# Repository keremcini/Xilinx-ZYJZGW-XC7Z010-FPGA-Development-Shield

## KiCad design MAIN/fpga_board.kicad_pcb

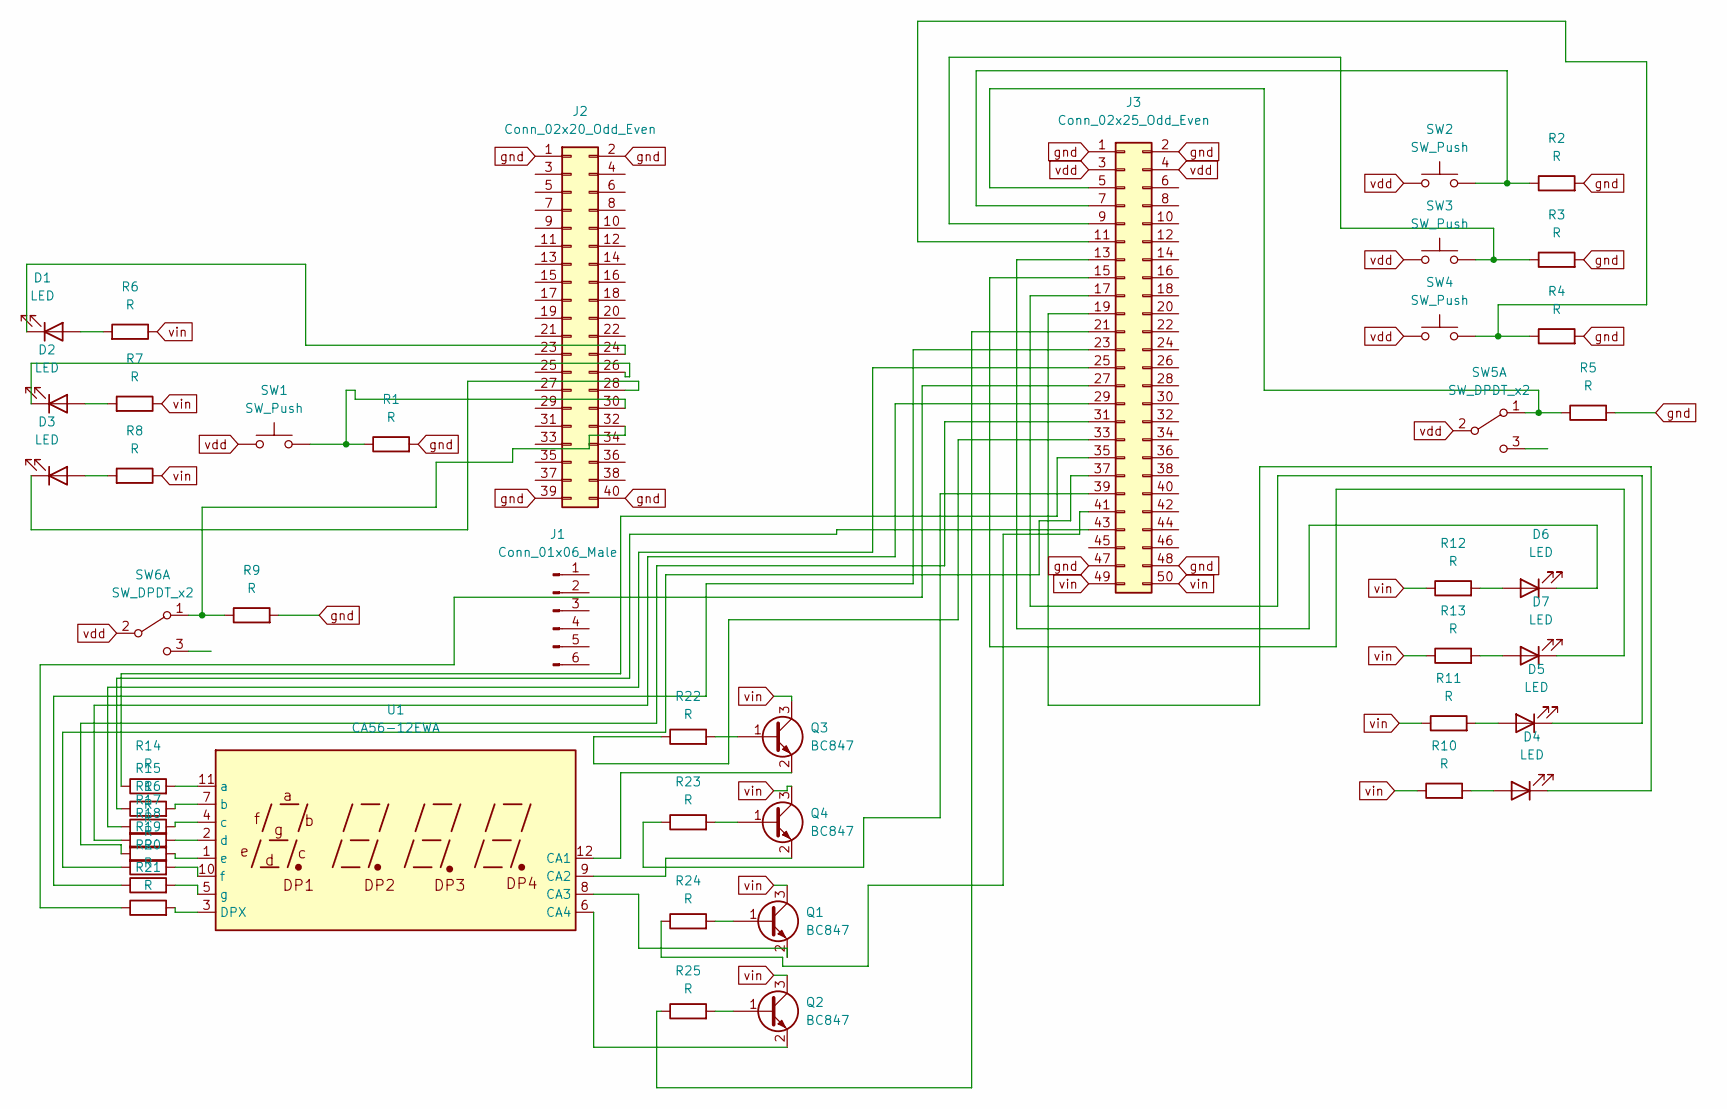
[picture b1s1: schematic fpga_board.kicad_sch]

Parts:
D1, D2, D3, D4, D5, D6, D7: LED; LED_0805_2012Metric_Pad1.15x1.40mm_HandSolder
J1: Conn_01x06_Male; PinHeader_1x06_P2.54mm_Vertical
J2: Conn_02x20_Odd_Even; PinHeader_2x20_P2.54mm_Vertical
J3: Conn_02x25_Odd_Even; PinHeader_2x25_P2.54mm_Vertical
Q1, Q2, Q3, Q4: BC847; SOT-23
R1, R2, R3, R4, R5, R6, R7, R8, R9, R10, R11, R12, R13, R14, R15, R16, R17, R18, R19, R20, R21, R22, R23, R24, R25: R; R_0805_2012Metric_Pad1.20x1.40mm_HandSolder
SW1, SW2, SW3, SW4: SW_Push; red_button
SW5, SW6: SW_DPDT_x2; switch_smd
U1: CA56-12EWA; 4_digit7_segment

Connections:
unnamed: D1.2 (A), R6.2
unnamed: D1.1 (K), J2.24
unnamed: D2.2 (A), R7.2
unnamed: D2.1 (K), J2.26
unnamed: D3.2 (A), R8.2
unnamed: D3.1 (K), J2.28
unnamed: D4.2 (A), R10.2
unnamed: D4.1 (K), J3.19
unnamed: D5.2 (A), R11.2
unnamed: D5.1 (K), J3.17
unnamed: D6.2 (A), R12.2
unnamed: D6.1 (K), J3.13
unnamed: D7.2 (A), R13.2
unnamed: D7.1 (K), J3.15
unnamed: J2.30, R1.1, SW1.2
unnamed: J2.32, R9.1, SW6.1 (A)
unnamed: J3.5, R5.1, SW5.1 (A)
unnamed: J3.7, R2.1, SW2.2
unnamed: J3.9, R3.1, SW3.2
unnamed: J3.11, R4.1, SW4.2
unnamed: J3.21, R25.1
unnamed: J3.23, R20.1
unnamed: J3.25, R16.1
unnamed: J3.27, R21.1
unnamed: J3.29, R17.1
unnamed: J3.31, R18.1
unnamed: J3.33, R22.1
unnamed: J3.35, R14.1
unnamed: J3.37, R19.1
unnamed: J3.39, R23.1
unnamed: J3.41, R24.1
unnamed: J3.43, R15.1
unnamed: Q1.1 (B), R24.2
unnamed: Q1.2 (E), U1.8 (CA3)
unnamed: Q2.1 (B), R25.2
unnamed: Q2.2 (E), U1.6 (CA4)
unnamed: Q3.1 (B), R22.2
unnamed: Q3.2 (E), U1.12 (CA1)
unnamed: Q4.1 (B), R23.2
unnamed: Q4.2 (E), U1.9 (CA2)
unnamed: R21.2, U1.3 (DPX)
unnamed: R14.2, U1.11 (a)
unnamed: R15.2, U1.7 (b)
unnamed: R16.2, U1.4 (c)
unnamed: R17.2, U1.2 (d)
unnamed: R18.2, U1.1 (e)
unnamed: R19.2, U1.10 (f)
unnamed: R20.2, U1.5 (g)
gnd: J2.1, J2.2, J2.39, J2.40, J3.1, J3.2, J3.47, J3.48, R1.2, R2.2, R3.2, R4.2, R5.2, R9.2
vdd: J3.3, J3.4, SW1.1, SW2.1, SW3.1, SW4.1, SW5.2 (B), SW6.2 (B)
vin: J3.49, J3.50, Q1.3 (C), Q2.3 (C), Q3.3 (C), Q4.3 (C), R6.1, R7.1, R8.1, R10.1, R11.1, R12.1, R13.1

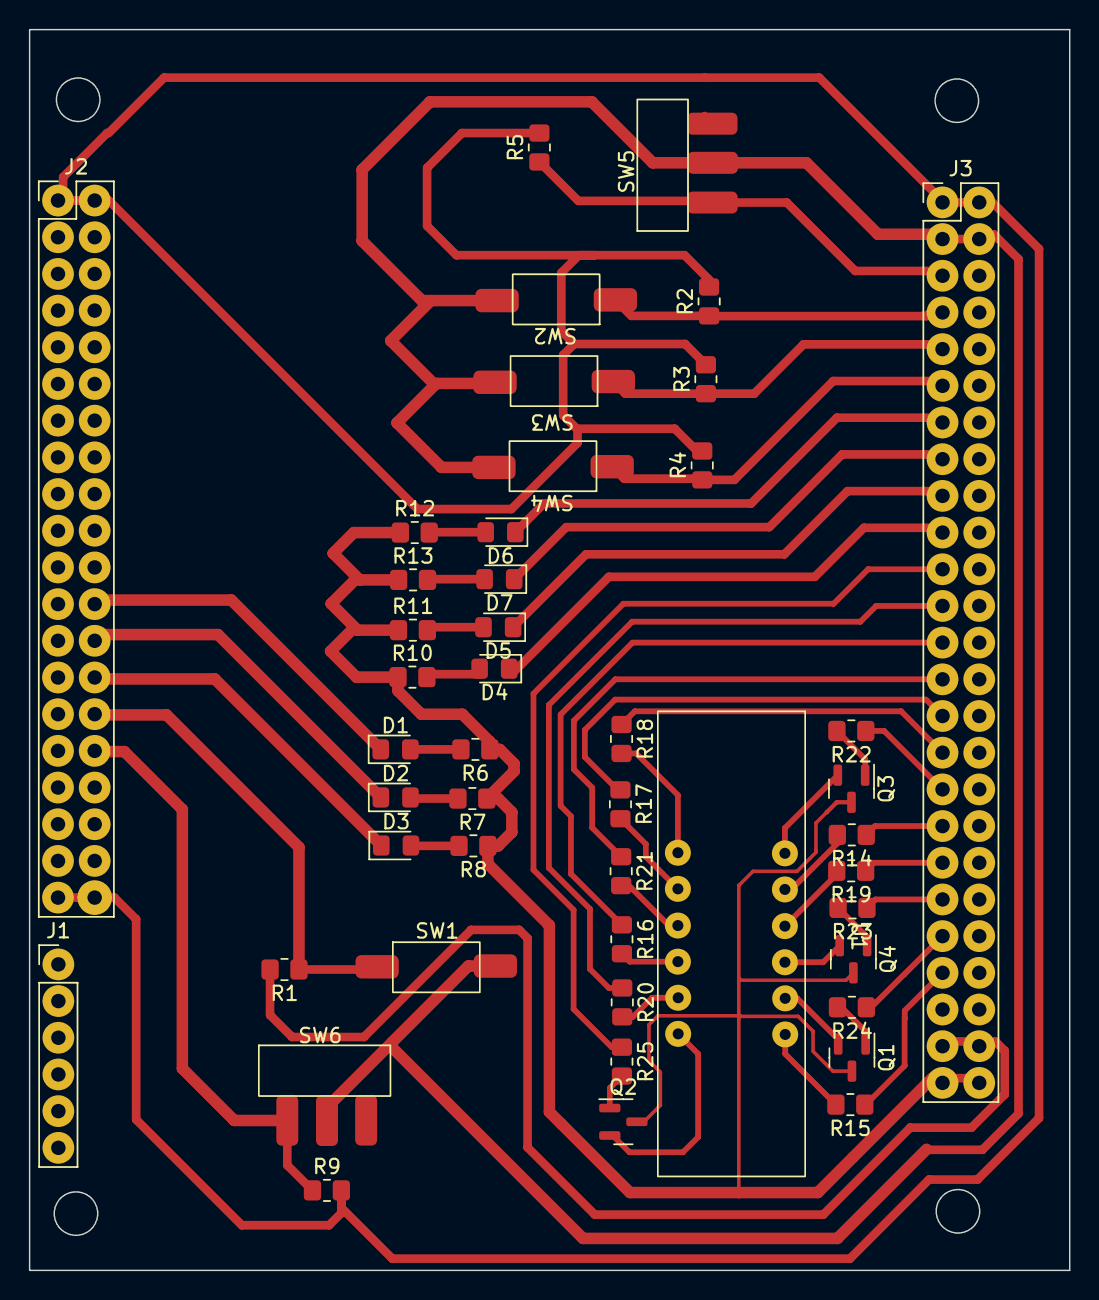
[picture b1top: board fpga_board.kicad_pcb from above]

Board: 2 copper layers, 72.0 x 85.9 mm, 46 parts (0 on the bottom side), 51 nets.

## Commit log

2023-07-16 Fpga shield
